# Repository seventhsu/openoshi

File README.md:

# OpenOshi
A fully open-source, DIY concert penlight. (v2.0)

Whether in the midst of the crowd at Belluna Dome or sitting in the dark in your bedroom, cheer on your favorite idols with this powerful, fully customizable penlight. It runs off of a single lithium battery and charges via USB-C to shine bright for hours of your favorite performances.

Best of all, it costs **less than $10 to make!** Total! That includes the PCB, the components, the battery, and the handle and tube! All while being fully hackable and modifiable. Manufacture in quantity and see how many you can hold in one hand: a classic idolfan challenge. 

This project consists of:
- a 3D-printable handle and screw-in translucent blade
- the Lightboard: a central PCB with an RGBW LED, a CH32V003F4U6 microcontroller, buttons and a USB-C charging port
- software to easily add your favorite idols' colors to your Lightboard

OpenOshi's electrical and mechanical components are open-source hardware licensed under CERN-OHL-S-2.0 (see the root `LICENSE` file). The firmware is open-source software licensed under the MIT License (see `firmware/LICENSE`). The `ch32fun` SDK included as a submodule of the firmware remains under its own MIT License; refer to the submodule's `LICENSE` file.

**Building tips**
- For printing the handle, I suggest a neutral color of PLA filament, and for the tube, transparent PETG printed at 100% rectilinear infill.
- The PCB is made to JLCPCB 2-layer specifications and tolerances as of July 2025. Modify if needed to meet your preferred PCB supplier's capabilities.
- The control firmware can be flashed to the board with a single wire using the SWIO programming pad on the top. To do so, you will need a WCH-Link programmer or equivalent and a flashing tool; [`ch32fun`](https://github.com/cnlohr/ch32fun) names several good open-source options like the `esp32s2-funprog` for the former, and it implements the `minichlink` tool for the latter.

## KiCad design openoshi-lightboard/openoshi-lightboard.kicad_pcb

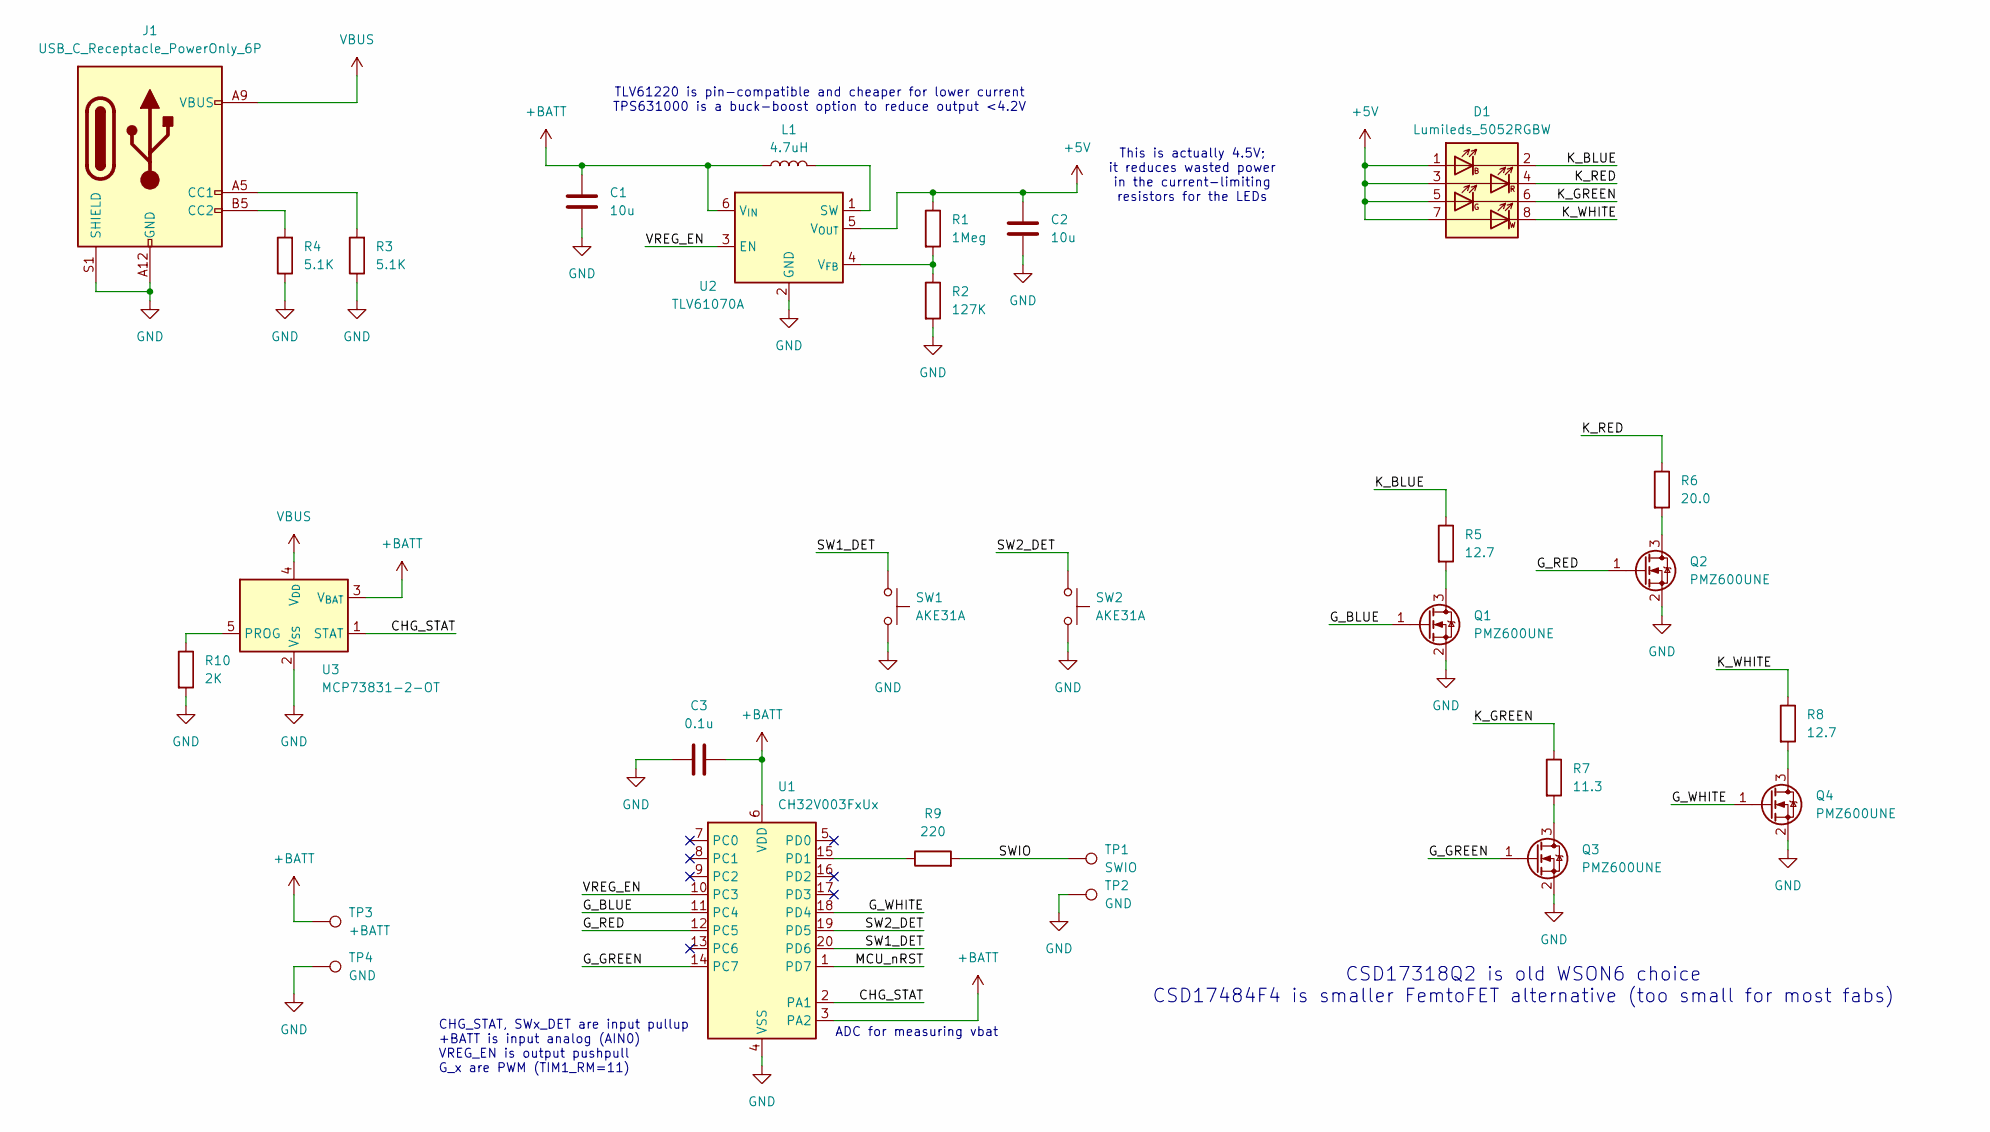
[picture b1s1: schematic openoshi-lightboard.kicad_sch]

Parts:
C1, C2: 10u; C_0603_1608Metric
C3: 0.1u; C_0603_1608Metric
D1: Lumileds_5052RGBW; LED_Lumileds_5052RGBW_LGA9_5.0x5.2mm_P0.5mm
J1: USB_C_Receptacle_PowerOnly_6P; USB_C_Receptacle_GCT_USB4125-xx-x_6P_TopMnt_Horizontal
L1: 4.7uH; L_1210_3225Metric
Q1, Q2, Q3, Q4: PMZ600UNE; SOT-883
R1: 1Meg; R_0603_1608Metric
R2: 127K; R_0603_1608Metric
R3, R4: 5.1K; R_0603_1608Metric
R5, R8: 12.7; R_1206_3216Metric
R6: 20.0; R_1206_3216Metric
R7: 11.3; R_1206_3216Metric
R9: 220; R_0603_1608Metric
R10: 2K; R_0603_1608Metric
SW1, SW2: AKE31A; SW_EVP-AKE31A_PAN
TP1: SWIO; TestPoint_Pad_D1.0mm
TP2: GND; TestPoint_Pad_D1.0mm
TP3: +BATT; Battery_SolderPad
TP4: GND; Battery_SolderPad
U1: CH32V003FxUx; QFN-20-1EP_3x3mm_P0.4mm_EP1.65x1.65mm
U2: TLV61070A; SOT-23-6
U3: MCP73831-2-OT; SOT-23-5

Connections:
+5V: C2.1, D1.1 (AB), D1.3 (AR), D1.5 (AG), D1.7 (AW), D1.9 (AR), R1.1, U2.5 (V_{OUT})
+BATT: C1.1, C3.2, L1.1, TP3.1, U1.3 (PA2), U1.6 (VDD), U2.6 (V_{IN}), U3.3 (V_{BAT})
/CHG_STAT: U1.2 (PA1), U3.1 (STAT)
/G_BLUE: Q1.1 (G), U1.11 (PC4)
/G_GREEN: Q3.1 (G), U1.14 (PC7)
/G_RED: Q2.1 (G), U1.12 (PC5)
/G_WHITE: Q4.1 (G), U1.18 (PD4)
/K_BLUE: D1.2 (KB), R5.1
/K_GREEN: D1.6 (KG), R7.1
/K_RED: D1.4 (KR), R6.1
/K_WHITE: D1.8 (KW), R8.1
/MCU_nRST: U1.1 (PD7)
/SW1_DET: SW1.1, U1.20 (PD6)
/SW2_DET: SW2.1, U1.19 (PD5)
/SWIO: R9.2, TP1.1
/VREG_EN: U1.10 (PC3), U2.3 (EN)
GND: C1.2, C2.2, C3.1, J1.A12 (GND), J1.B12 (GND), J1.S1 (SHIELD), Q1.2 (S), Q2.2 (S), Q3.2 (S), Q4.2 (S), R2.2, R3.1, R4.1, R10.2, SW1.2, SW2.2, TP2.1, TP4.1, U1.4 (VSS), U1.21 (VSS), U2.2 (GND), U3.2 (V_{SS})
unnamed: J1.A5 (CC1), R3.2
unnamed: J1.B5 (CC2), R4.2
unnamed: Q1.3 (D), R5.2
unnamed: Q2.3 (D), R6.2
unnamed: Q3.3 (D), R7.2
unnamed: Q4.3 (D), R8.2
unnamed: R9.1, U1.15 (PD1)
unnamed: L1.2, U2.1 (SW)
unnamed: R1.2, R2.1, U2.4 (V_{FB})
unnamed: R10.1, U3.5 (PROG)
VBUS: J1.A9 (VBUS), J1.B9 (VBUS), U3.4 (V_{DD})

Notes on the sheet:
This is actually 4.5V; it reduces wasted power in the current-limiting resistors for the LEDs
CSD17318Q2 is old WSON6 choice CSD17484F4 is smaller FemtoFET alternative (too small for most fabs)
TLV61220 is pin-compatible and cheaper for lower current TPS631000 is a buck-boost option to reduce output <4.2V
CHG_STAT, SWx_DET are input pullup +BATT is input analog (AIN0) VREG_EN is output pushpull G_x are PWM (TIM1_RM=11)
ADC for measuring vbat

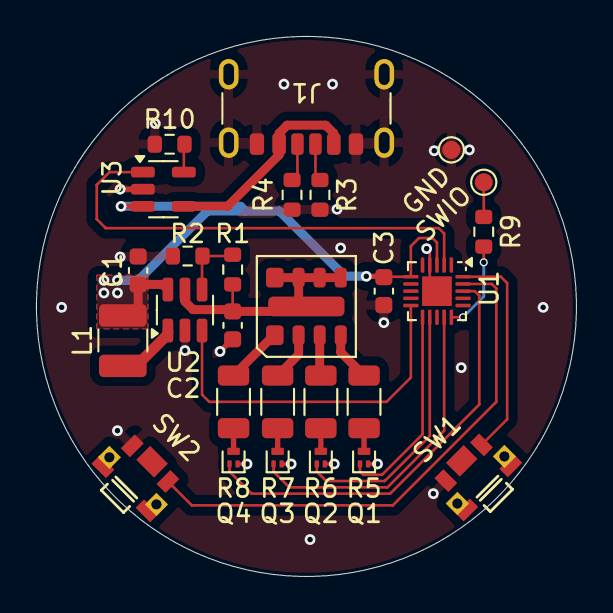
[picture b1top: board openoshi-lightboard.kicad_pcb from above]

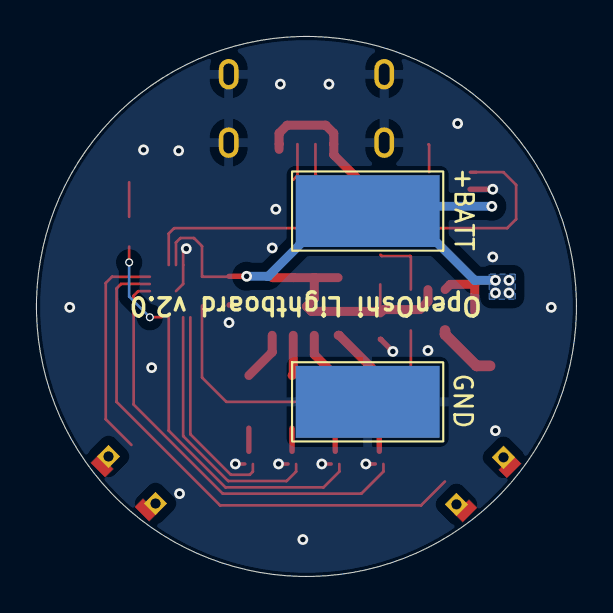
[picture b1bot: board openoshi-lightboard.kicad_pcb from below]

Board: 2 copper layers, 30.0 x 30.0 mm, 29 parts (2 on the bottom side), 27 nets.

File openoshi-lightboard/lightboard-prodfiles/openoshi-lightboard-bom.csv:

Comment,Designator,Footprint,LCSC Part Number
10u,"C1,C2",Capacitor_SMD:C_0603_1608Metric,C19702
0.1u,C3,Capacitor_SMD:C_0603_1608Metric,C14663
USB_C_Receptacle_PowerOnly_6P,J1,Connector_USB:USB_C_Receptacle_GCT_USB4125-xx-x_6P_TopMnt_Horizontal,C668623
4.7uH,L1,Inductor_SMD:L_1210_3225Metric,C703083
PMZ600UNE,"Q1,Q2,Q3,Q4",Package_TO_SOT_SMD:SOT-883,C547286
1Meg,R1,Resistor_SMD:R_0603_1608Metric,C105578
127K,R2,Resistor_SMD:R_0603_1608Metric,C245905
5.1K,"R3,R4",Resistor_SMD:R_0603_1608Metric,C105580
12.7,"R5,R8",Resistor_SMD:R_1206_3216Metric,C870404
20,R6,Resistor_SMD:R_1206_3216Metric,C114941
11.3,R7,Resistor_SMD:R_1206_3216Metric,C870385
220,R9,Resistor_SMD:R_0603_1608Metric,C107696
2K,R10,Resistor_SMD:R_0603_1608Metric,C105576
AKE31A,"SW1,SW2",openoshi-lightboard:SW_EVP-AKE31A_PAN,C569760
CH32V003FxUx,U1,Package_DFN_QFN:QFN-20-1EP_3x3mm_P0.4mm_EP1.65x1.65mm,C5299908
TLV61070A,U2,Package_TO_SOT_SMD:SOT-23-6,C6881375
TP4054,U3,Package_TO_SOT_SMD:SOT-23-5,C668215

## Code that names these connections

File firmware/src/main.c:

// SPDX-License-Identifier: MIT
// Copyright (c) 2025-2026 Seventhsu

#include "../ch32fun/ch32fun/ch32fun.h"
#include <stdio.h>

#define PERIPH_CLOCK FUNCONF_SYSTEM_CORE_CLOCK  // HPRE=DIV1 after SystemInit

#define LED_PWM_MAX_FREQ_HZ 1000 // Change me at your leisure!
#define COLOR_BIT_DEPTH 8

#define NUM_COLORS     (sizeof(colorTable) / sizeof(colorTable[0]))
#define DEBOUNCE_MS    30
#define LONG_PRESS_MS  800
#define POLL_MS        10

// colorTable[i][0:3] represent B, G, R, W channels of one color setting
uint8_t colorTable[][4] = {
	{0x0,	0x0,	0xff,	0x0},   // Color red
    {0x0,	0xff,	0xff,	0x0},   // Color yellow
	{0x0,	0xff,	0x0,	0x0},   // Color green
    {0xff,	0xff,	0x0,	0x0},   // Color cyan
	{0xff,	0x0,	0x0,	0x0},   // Color blue
    {0xff,	0x0,	0xff,	0x0},   // Color magenta
	{0x0,	0x0,	0x0,	0xff},  // Color white
};

// The color the penlight should display if it was on (index into colorTable)
static volatile int currColor;

// Bitmask set by ISR: bit 0 = SW1 (PD6), bit 1 = SW2 (PD5)
static volatile uint8_t btnEvent;

void EXTI7_0_IRQHandler(void) __attribute__((interrupt));
void EXTI7_0_IRQHandler(void) {
    if (EXTI->INTFR & EXTI_Line6)  btnEvent |= 0x01;  // SW1
    if (EXTI->INTFR & EXTI_Line5)  btnEvent |= 0x02;  // SW2
    EXTI->INTFR = EXTI_Line6 | EXTI_Line5;          // Acknowledge both
}

void tim1PwmInit(void) {
    RCC->APB2PCENR |= RCC_APB2Periph_TIM1;

    // Map and AF-configure pins to be used by TIM1
    // TIM1 map: CH1=PC4(blue), CH2=PC7(green), CH3=PC5(red), CH4=PD4(white)
    AFIO->PCFR1 |= AFIO_PCFR1_TIM1_REMAP_FULLREMAP;
    funPinMode(PC4, GPIO_CFGLR_OUT_2Mhz_AF_PP); // blue LED
    funPinMode(PC7, GPIO_CFGLR_OUT_2Mhz_AF_PP); // green LED
    funPinMode(PC5, GPIO_CFGLR_OUT_2Mhz_AF_PP); // red LED
    funPinMode(PD4, GPIO_CFGLR_OUT_2Mhz_AF_PP); // white LED

    // Reset TIM1 to init all regs
    RCC->APB2PRSTR |= RCC_APB2Periph_TIM1;
	RCC->APB2PRSTR &= ~RCC_APB2Periph_TIM1;

    /* Yes, the colors could have better than 8-bit depth
     * if the prescaler was set to 0 and autoreload was larger.
     * But 8-bit color is well-documented and easy to work with.
     */
    // Autoreload (PWM period) is set so that 8-bit duty cycle values match its range
    // PSC is calculated such that the actual PWM freq is <= LED_PWM_MAX_FREQ_HZ
    const uint32_t autoreload = (1<<COLOR_BIT_DEPTH) - 1; // 255
    TIM1->PSC = (PERIPH_CLOCK / (LED_PWM_MAX_FREQ_HZ * (autoreload + 1)));
    TIM1->ATRLR = autoreload;

    // Set mode = b110 (PWM mode 1, left aligned) and enable shadow regs ("preload") for all
    TIM1->CHCTLR1 |= TIM_OC2M_2 | TIM_OC2M_1 | TIM_OC2PE | TIM_OC1M_2 | TIM_OC1M_1 | TIM_OC1PE;
    TIM1->CHCTLR2 |= TIM_OC4M_2 | TIM_OC4M_1 | TIM_OC4PE | TIM_OC3M_2 | TIM_OC3M_1 | TIM_OC3PE;

    // CTLR1 defaults to up-count, UEVs generated (auto-copy from shadow reg), edge align
	TIM1->CTLR1 |= TIM_ARPE; // enable auto-reload of preload

    TIM1->CCER |= TIM_CC4E | TIM_CC3E | TIM_CC2E | TIM_CC1E; // All channels output enable

    // Kickstart the counter with a UG bit set
    TIM1->SWEVGR |= TIM_UG;
    TIM1->CTLR1 |= TIM_CEN;
    TIM1->BDTR |= TIM_MOE; // Main Output Enable required for advanced timer TIM1
}

void updateColor(void) {
    TIM1->CH1CVR = (uint32_t) colorTable[currColor][0];
    TIM1->CH2CVR = (uint32_t) colorTable[currColor][1];
    TIM1->CH3CVR = (uint32_t) colorTable[currColor][2];
    TIM1->CH4CVR = (uint32_t) colorTable[currColor][3];
}

void extiInit(void) {
    // Map PD5 -> EXTI5, PD6 -> EXTI6
    AFIO->EXTICR |= AFIO_EXTICR_EXTI5_PD | AFIO_EXTICR_EXTI6_PD;

    // Enable interrupt (for WFI wake) and event (for WFE wake) on lines 5 and 6
    EXTI->INTENR |= EXTI_INTENR_MR5 | EXTI_INTENR_MR6;
    EXTI->EVENR  |= EXTI_EVENR_MR5  | EXTI_EVENR_MR6;

    // Falling edge trigger (buttons are active-low with pull-ups)
    EXTI->FTENR  |= EXTI_FTENR_TR5  | EXTI_FTENR_TR6;

    NVIC_EnableIRQ(EXTI7_0_IRQn);
}

void enterStandby(void) {
    // Turn off LED outputs
    TIM1->CH1CVR = 0; TIM1->CH2CVR = 0;
    TIM1->CH3CVR = 0; TIM1->CH4CVR = 0;

    // Disable boost converter
    funDigitalWrite(PC3, FUN_LOW);

    // Configure for standby wake
    RCC->APB1PCENR |= RCC_APB1Periph_PWR;
    PWR->CTLR |= PWR_CTLR_PDDS;
    PFIC->SCTLR |= (1 << 2); // SLEEPDEEP

    // Wait for button release before sleeping (avoid instant wake)
    while (funDigitalRead(PD6) == 0 || funDigitalRead(PD5) == 0)
        Delay_Ms(10);
    Delay_Ms(DEBOUNCE_MS);

    // Clear any pending EXTI events
    EXTI->INTFR = EXTI_Line6 | EXTI_Line5;

    // Enter deep standby (WFE)
    __WFE();
}

void exitStandby(void) {
    SystemInit();                       // Restore PLL and clocks
    PFIC->SCTLR &= ~(1 << 2);           // Clear SLEEPDEEP for WFI mode
    funDigitalWrite(PC3, FUN_HIGH);     // Re-enable boost converter
    Delay_Ms(5);                        // Let boost converter stabilize
    updateColor();                      // Restore saved color to PWM

    // Debounce the wake button press
    while (funDigitalRead(PD6) == 0 || funDigitalRead(PD5) == 0)
        Delay_Ms(10);
    Delay_Ms(DEBOUNCE_MS);
    btnEvent = 0;                       // Clear any events from the wake press
}

uint16_t readBatteryMv(void) {
    // Enable internal Vrefint on ADC channel 8
    ADC1->CTLR2 |= ADC_TSVREFE;

    // Read internal 1.2V reference (channel 8)
    uint16_t vref_raw = funAnalogRead(ADC_Channel_Vrefint);

    // Disable Vrefint to save power
    ADC1->CTLR2 &= ~ADC_TSVREFE;

    // VDD = Vrefint_known * ADC_max / vref_raw
    // In mV: (1200 * 1023) / vref_raw
    if (vref_raw == 0) return 0; // Guard against division by zero
    return (uint16_t)((1200UL * 1023) / vref_raw);
}

int main(void) {
    SystemInit();
    Delay_Ms(5000); // Reprogramming window: allow reflashing before sleep

    funGpioInitAll(); // Enables AFIO + ports A C D

    tim1PwmInit();
    funAnalogInit(); // Initialize ADC via ch32fun helper

    // Assign directions to general-purpose pins
    funPinMode(PA1, GPIO_CFGLR_IN_PUPD);        // batt CHG_STAT
    //funPinMode(PA2, GPIO_CFGLR_IN_ANALOG);      // vbatt adc, on AIN0
    funPinMode(PC3, GPIO_CFGLR_OUT_2Mhz_PP);    // VREG_EN
    funPinMode(PD6, GPIO_CFGLR_IN_PUPD);        // SW1
    funPinMode(PD5, GPIO_CFGLR_IN_PUPD);        // SW2
    // Explicitly enable input-pullup resistors for SWy by writing to GPIOx_OUTDR
    funDigitalWrite(PD6, FUN_HIGH);
    funDigitalWrite(PD5, FUN_HIGH);

    // Configure EXTI for button interrupts and events
    extiInit();

    // Write timer duty cycles to display first color
    currColor = 0;
    updateColor();

    // Enable power supply by asserting VREG_EN, thus turning on the LED
    funDigitalWrite(PC3, FUN_HIGH);

    while (1) {
        // WFI in loop ensures mcu always goes to sleep when not doing anything
        __WFI(); // Wait For (button) Interrupt

        /*
         * At this point the light is active and the mcu can sleep. The button interrupts
         * wake the mcu from WFI, and their ISRs simply set a flag and return execution to
         * the loop code below. This code reads the flag, debounces the button, and if
         * short-pressed, sends a new color to TIM1 and reenters sleep. If long-pressed (user
         * wants to turn off the device), it should disable the light and the boost conv,
         * then WFE (standby).
         */
        
        if (!btnEvent) continue; // Spurious wake
        uint8_t btn = btnEvent;
        btnEvent = 0;

        // Software debounce
        Delay_Ms(DEBOUNCE_MS);

        // Determine which pin to poll (pick first if both pressed)
        uint8_t pin = (btn & 0x01) ? PD6 : PD5;

        if (funDigitalRead(pin) != 0) continue; // Bounced away, ignore

        // Long press detection: poll until release or timeout
        uint16_t held = DEBOUNCE_MS;
        while (funDigitalRead(pin) == 0 && held < LONG_PRESS_MS) {
            Delay_Ms(POLL_MS);
            held += POLL_MS;
        }

        if (held >= LONG_PRESS_MS) {
            // LONG PRESS: transition to LED_OFF (standby)
            enterStandby();
            // Execution resumes here after WFE wake
            exitStandby();
        } else {
            // SHORT PRESS: cycle color
            if (btn & 0x01) {
                currColor = (currColor + 1) % NUM_COLORS; // SW1: forward
            } else {
                currColor = (currColor + NUM_COLORS - 1) % NUM_COLORS; // SW2: backward
            }
            updateColor();
        }
    }
    return 0;
}

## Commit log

2023-06-03 Create text
2023-06-03 Rename pcb1.gbl to lightboard-gerbers/pcb1.gbl
2023-06-03 Moved gerbars into lightboard-gerbers/
2023-08-11 Preliminary software upload
2025-04-22 work on v2.0 has begun
2025-04-27 added pictures to readme
2025-04-29 updated readme and part names
2025-05-14 added LED
2025-05-14 Remove backups from repo
2025-06-23 Safety upgrades all around
2025-07-09 Tentative sch completion, initial layout
2025-07-19 Prepping for large reroute
2025-07-22 Reroute complete
2025-07-23 Assembly files created, first run
2025-08-06 Begin firmware work
2025-08-11 Imported ch32fun lib, begun work on main.c
2025-09-14 more progress on pin cfg
2025-09-15 Completed ledpwm code
2025-11-06 Updated pictures
2025-11-06 add new images to README
2026-02-06 Major refactor, moved to ch32fun submodule
2026-02-07 Implement WFE, buttons irq and debounce
2026-02-07 Improved fw build and lint experience
2026-02-07 Dredged up and archived v1.0 assets
2026-02-09 Clarified project license structure
2026-02-12 Added function to measure Vbatt
